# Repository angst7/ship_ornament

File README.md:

# ship_ornament
Starship Christmas tree ornament (KiCad)

This is a quick christmas tree ornament that I built with my daughter.  It features LEDs on each nacelle, an LED over the bridge area, and an LED on the reflector.

The LEDs are routed to four PWM output pins of an 14 pin TSSOT STM32L011 to allow flexibility in the light output level and the ability to do some lighting tricks.  If a microcontroller isn't desired, current limiting resistors can be populated for each LED, and the battery can be soldered directly to the resistors.

The battery is a CR2032.  The footprint is for part BAT-HLD-001 available at digikey and mouser. 

All the passives and LEDs are 0603.

The programming header is for a TC-2030-NL by Tag Connect.  Or you can just solder leads to the pads and use anything you like.

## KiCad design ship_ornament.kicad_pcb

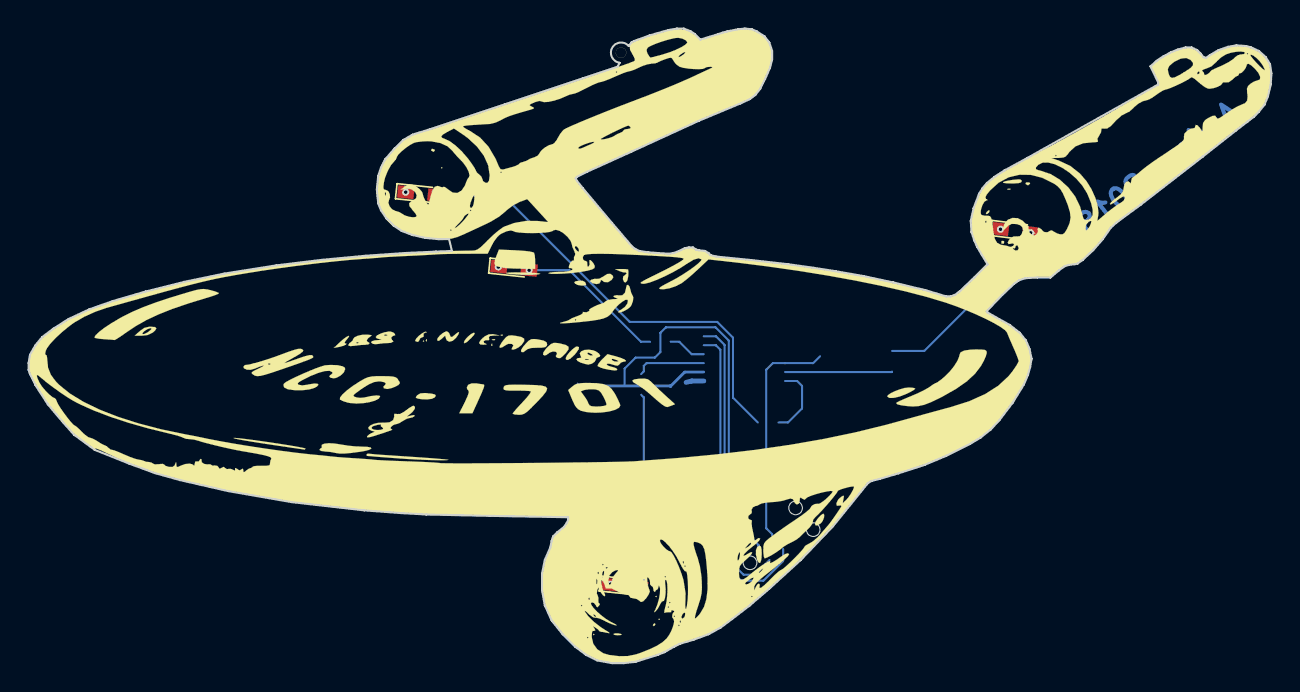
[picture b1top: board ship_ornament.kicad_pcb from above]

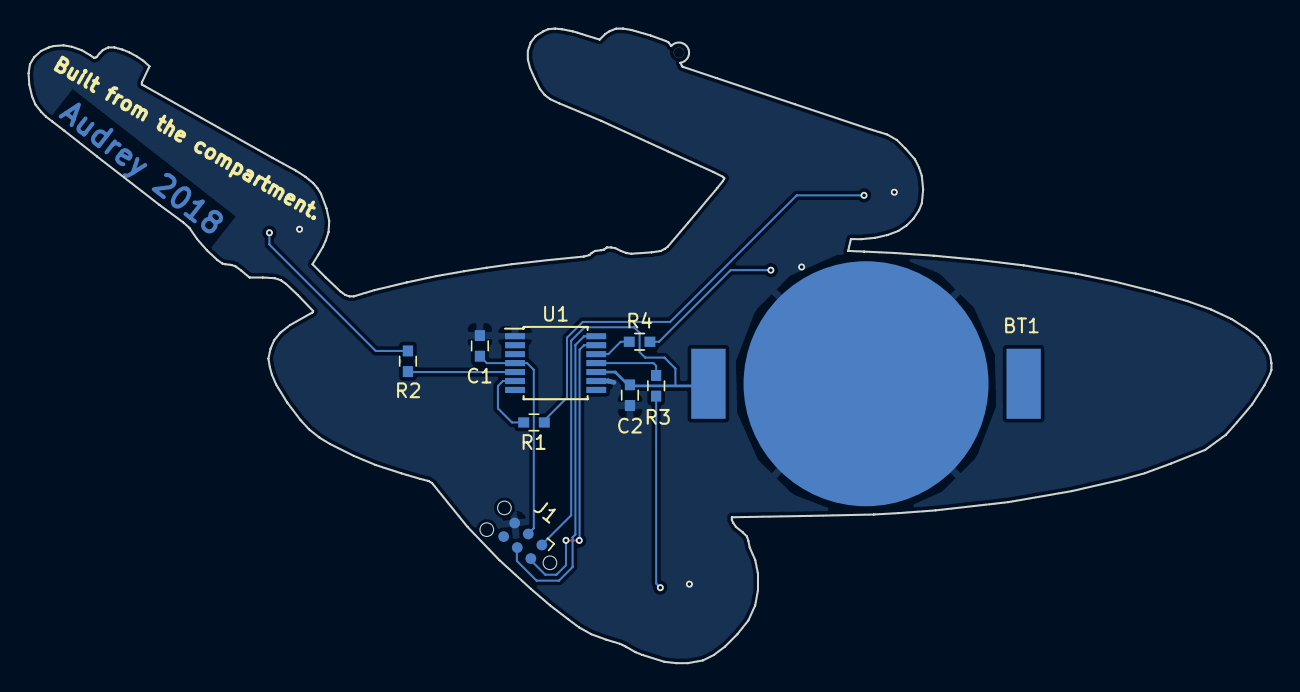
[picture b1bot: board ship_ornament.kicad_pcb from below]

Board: 2 copper layers, 90.3 x 46.1 mm, 13 parts (9 on the bottom side), 13 nets.

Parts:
BT1: Battery_Cell; BATT-HLD-001
C1, C2: 0.1uF; C_0603
D1, D2, D3, D4: LED_Small; LED_0603_HandSoldering
J1: Conn_02x03_Odd_Even; Tag-Connect_TC2030-IDC-NL
R1, R2, R3, R4: 520; C_0603
U1: STM32L011D3Px; TSSOP-14_4.4x5mm_Pitch0.65mm

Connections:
+BATT: BT1.1, C2.2, J1.1, U1.10
/BLUE_LED: R3.1, U1.11
/NRST: C1.2, J1.3, U1.4
/RED_LED1: R1.1, U1.6
/RED_LED2: R2.1, U1.5
/SWCLK: J1.4, U1.14
/SWDIO: J1.2, U1.13
/WHT_LED: R4.1, U1.12
GND: BT1.2, C1.1, C2.1, D1.1, D2.1, D3.1, D4.1, J1.5, U1.1, U1.9
unnamed: D1.2, R1.2
unnamed: D2.2, R2.2
unnamed: D3.2, R3.2
unnamed: D4.2, R4.2

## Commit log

2018-11-11 Initial commit of starship christmas ornament
